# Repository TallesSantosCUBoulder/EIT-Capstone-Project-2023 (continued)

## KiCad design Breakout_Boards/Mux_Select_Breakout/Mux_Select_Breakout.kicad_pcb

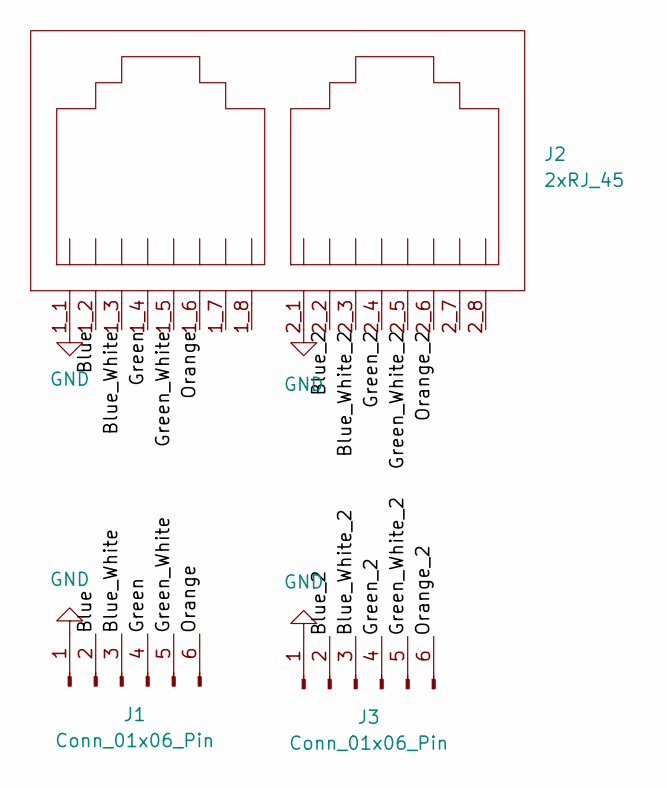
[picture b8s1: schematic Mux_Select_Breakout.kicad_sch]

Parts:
J1, J3: Conn_01x06_Pin; PinSocket_1x06_P2.54mm_Vertical
J2: 2xRJ_45; TE_2xRJ45

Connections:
/Ethernet_Breakout/Blue: J1.2, J2.1_2
/Ethernet_Breakout/Blue_2: J2.2_2, J3.2
/Ethernet_Breakout/Blue_White: J1.3, J2.1_3
/Ethernet_Breakout/Blue_White_2: J2.2_3, J3.3
/Ethernet_Breakout/Green: J1.4, J2.1_4
/Ethernet_Breakout/Green_2: J2.2_4, J3.4
/Ethernet_Breakout/Green_White: J1.5, J2.1_5
/Ethernet_Breakout/Green_White_2: J2.2_5, J3.5
/Ethernet_Breakout/Orange: J1.6, J2.1_6
/Ethernet_Breakout/Orange_2: J2.2_6, J3.6
GND: J1.1, J2.1_1, J2.2_1, J3.1

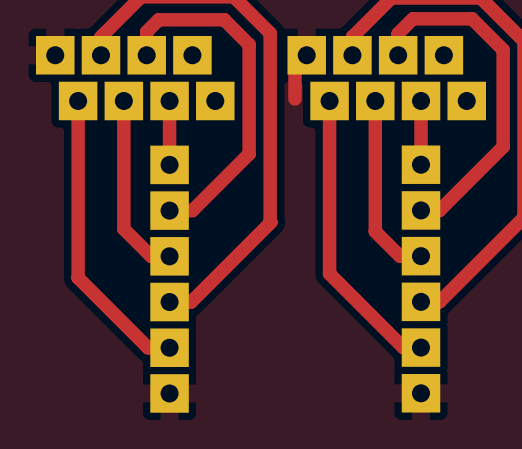
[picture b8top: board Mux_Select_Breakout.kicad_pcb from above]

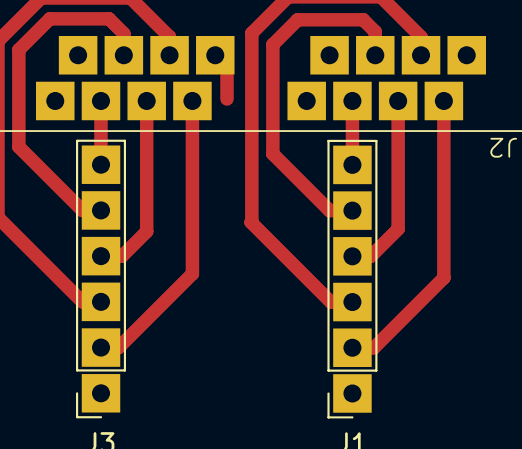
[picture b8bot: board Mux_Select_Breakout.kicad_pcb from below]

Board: 2 copper layers, 3 parts (3 on the bottom side), 11 nets.

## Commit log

2023-09-22 Create LICENSE
2023-11-08 First push of code
    Taken a while to push code sorry
2023-11-10 Update to Demodulation
2023-11-11 Fixed generalized multi-frequency wave generation
2023-11-11 Mostly Commented Control Script with updated wave generation code
2023-11-11 Control Script
2023-11-12 Improved control script and demodulation error test script
2023-11-13 Error test update
2023-11-13 Error Testing No Progress
2023-11-15 Fixed Multi-Frequency Generation
2023-11-17 Mux stepping using digital pins from NI board
2023-11-19 Start of Mux Function
2023-11-19 Finished Mux Control Function
2023-11-19 add setup for moving to python
2023-12-06 Demo Code for Mux
2023-12-06 Adding stuff to not add
2023-12-07 Python Connection
2023-12-08 Testing Second Python Library
2024-01-08 py digital output test
2024-01-09 channel swtiching
2024-01-09 Testing second library
2024-01-12 Testing Stream Readers
2024-01-16 Working on continous read
2024-01-22 Testing Different Task Setup
2024-01-24 Create delete
2024-01-24 Move files to right folder
2024-01-24 Testing Multi-Device Collection
2024-02-14 Testing Mux and Howland Together
2024-03-01 New folder for control script and adding phase to the sin function
2024-03-01 Moved info around
2024-03-01 Split control script to its own folder.
2024-03-01 Second round of system testing
2024-03-08 labeled pinout
2024-03-11 Add active electrode to project
2024-03-14 Active Electrode
2024-03-15 Modularize control script
2024-03-15 MUX PCB and schematic files
    This is the MUX PCB and schematic files for KICAD. The MUX PCB was changed to include load resistors which did not get incorporated. You might not find the PCB to be as helpful to look at as you migh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
2024-03-15 Control Scipt Work
2024-03-18 Mill Digital Select breakout board and more active electrodes
2024-03-18 Corrections made to active electrode and made 2 more
2024-03-18 Create blank
2024-03-18 Update and rename BLANK to README
2024-03-18 Rename README.md to Howland.md
2024-03-18 Updated Control Script, added active electrode switching and veriffied channels
2024-03-19 Updates to control script and tesing of the switches.
2024-03-30 Updated active electrode and other boards
2024-03-30 Create an electrode select breakout board
2024-04-02 Push Electrode_Breakout to Git
2024-04-05 Push current control script
2024-04-06 End of 8 electrode testing day 2
2024-04-07 Start of full system wiring diagram
2024-04-07 Update Wire Diagram
2024-04-07 End of 8 electrode testing day 3
2024-04-07 Final push from lab day 3
2024-04-10 Push update demodulation error test and updated duel mux
2024-04-10 Push new script for data collection and updated main script
2024-04-11 Push updated milling
2024-04-12 Update control scripts and add mat files for processing
2024-04-12 Updated the collected data to use the same rank restance and add the 10k sample run
2024-04-12 Pushing start of Design_Report.tex
2024-04-13 Testing functions to see output
2024-04-13 Update Data for Santos
2024-04-13 Updated Samples
2024-04-13 Object Testing
2024-04-13 Push updates for control scripts
2024-04-13 Push testing updates
2024-04-15 Start implementing image generation
2024-04-15 Push working imaging script
2024-04-16 Update demodulation calculations
2024-04-17 Using faster demod function
2024-04-19 Updated data collection for 16 electrodes
2024-04-19 Push update
2024-04-19 Test converting MATLAB to C++
2024-04-19 Push 16 electrode data for reconstruction
2024-04-20 Push to main
2024-04-21 Mulit Device unsynchronised
2024-04-21 Using ChatGPT to convert from MATLAB to Python
2024-04-22 Python conversion updates
2024-04-22 Everything works execpt analog output
2024-04-24 Push Semi Working Code
2024-04-26 Mostly working
2024-04-26 Update image plotting
2024-04-26 8 electrodes working
2024-05-06 Final code push for system
2024-06-03 Reorganization and updating README
2024-06-03 Modify README
2024-06-03 Update README.md
    Add Video
2024-06-03 Add Gif
2024-06-03 Update README.md
    Using gif for auto play
2024-08-18 Update README and main python script
